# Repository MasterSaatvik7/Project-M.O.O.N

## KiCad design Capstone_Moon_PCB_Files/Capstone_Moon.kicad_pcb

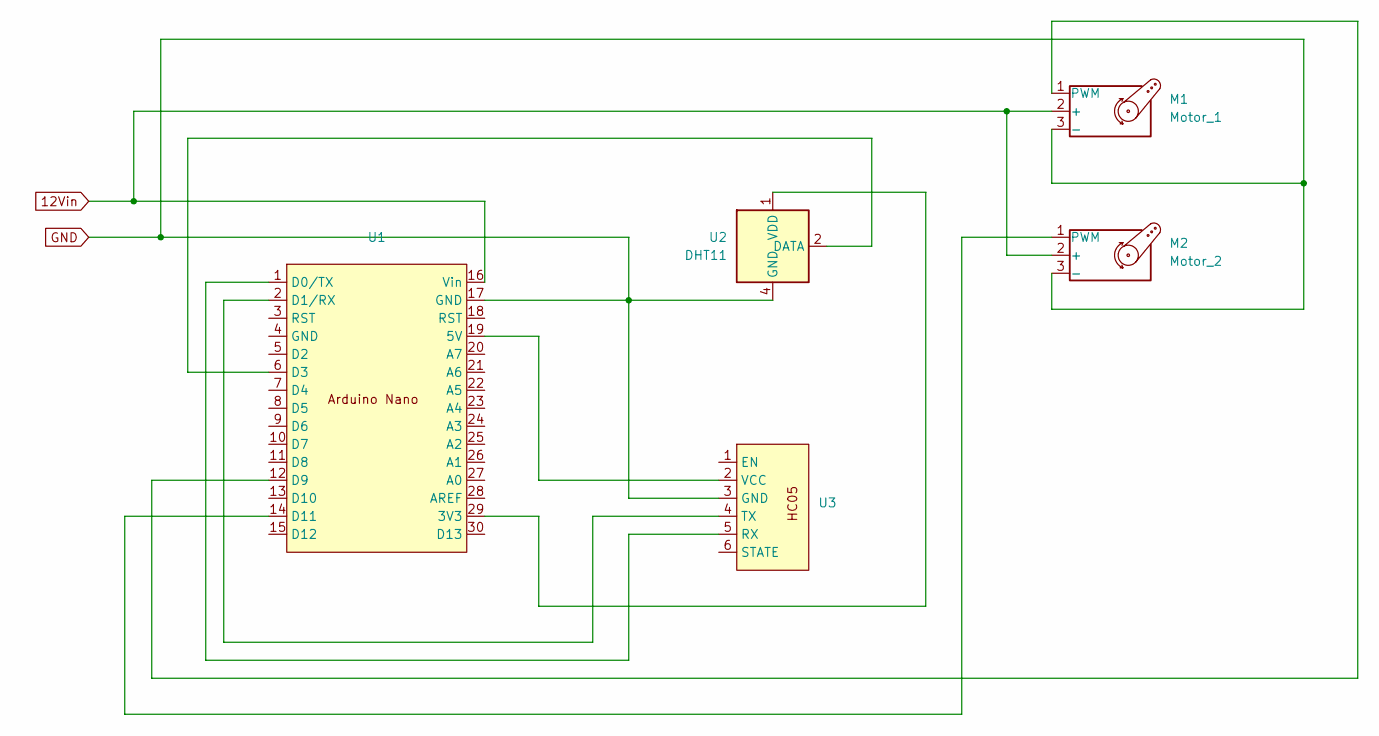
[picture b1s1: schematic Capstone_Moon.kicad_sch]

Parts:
M1: Motor_1; BLDC_temporary_pad
M2: Motor_2; BLDC_temporary_pad
U1: Arduino_Nano
U2: DHT11; Aosong_DHT11_5.5x12.0_P2.54mm
U3: HC05

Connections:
12Vin: M1.2 (+), M2.2 (+), U1.16 (Vin)
GND: M1.3 (-), M2.3 (-), U1.17 (GND), U2.4 (GND), U3.3 (GND)
unnamed: M1.1 (PWM), U1.12 (D9)
unnamed: M2.1 (PWM), U1.14 (D11)
unnamed: U1.29 (3V3), U2.1 (VDD)
unnamed: U1.19 (5V), U3.2 (VCC)
unnamed: U1.1 (D0/TX), U3.5 (RX)
unnamed: U1.2 (D1/RX), U3.4 (TX)
unnamed: U1.6 (D3), U2.2 (DATA)

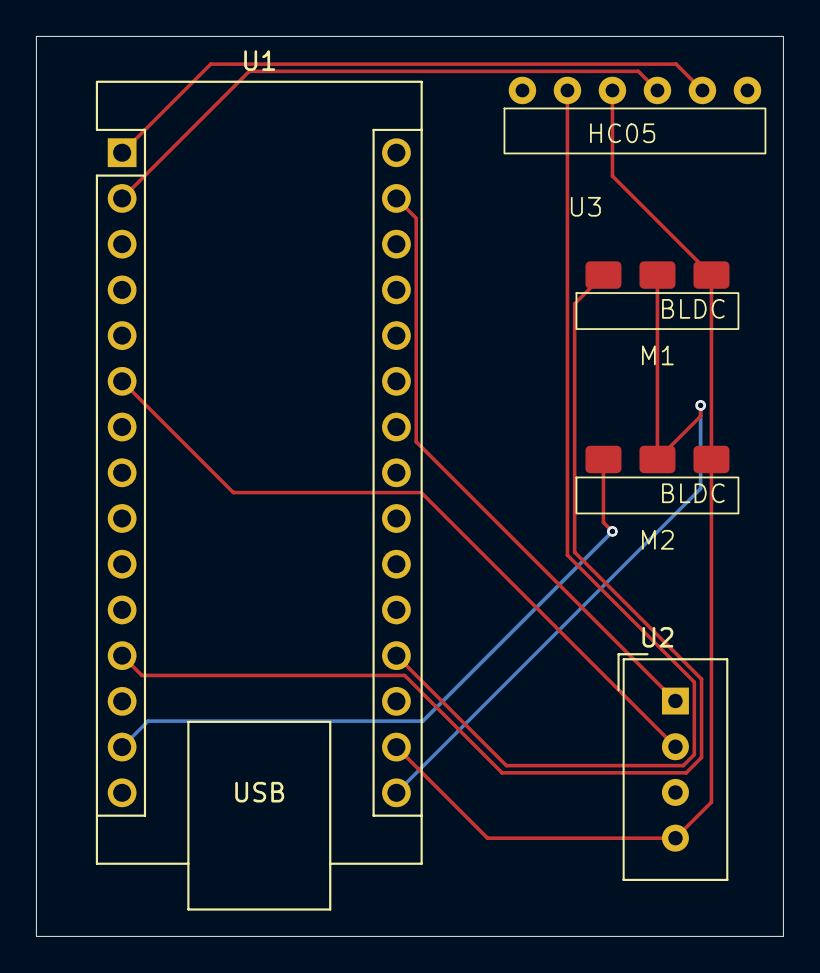
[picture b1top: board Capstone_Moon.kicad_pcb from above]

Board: 2 copper layers, 41.5 x 50.0 mm, 5 parts (0 on the bottom side), 9 nets.

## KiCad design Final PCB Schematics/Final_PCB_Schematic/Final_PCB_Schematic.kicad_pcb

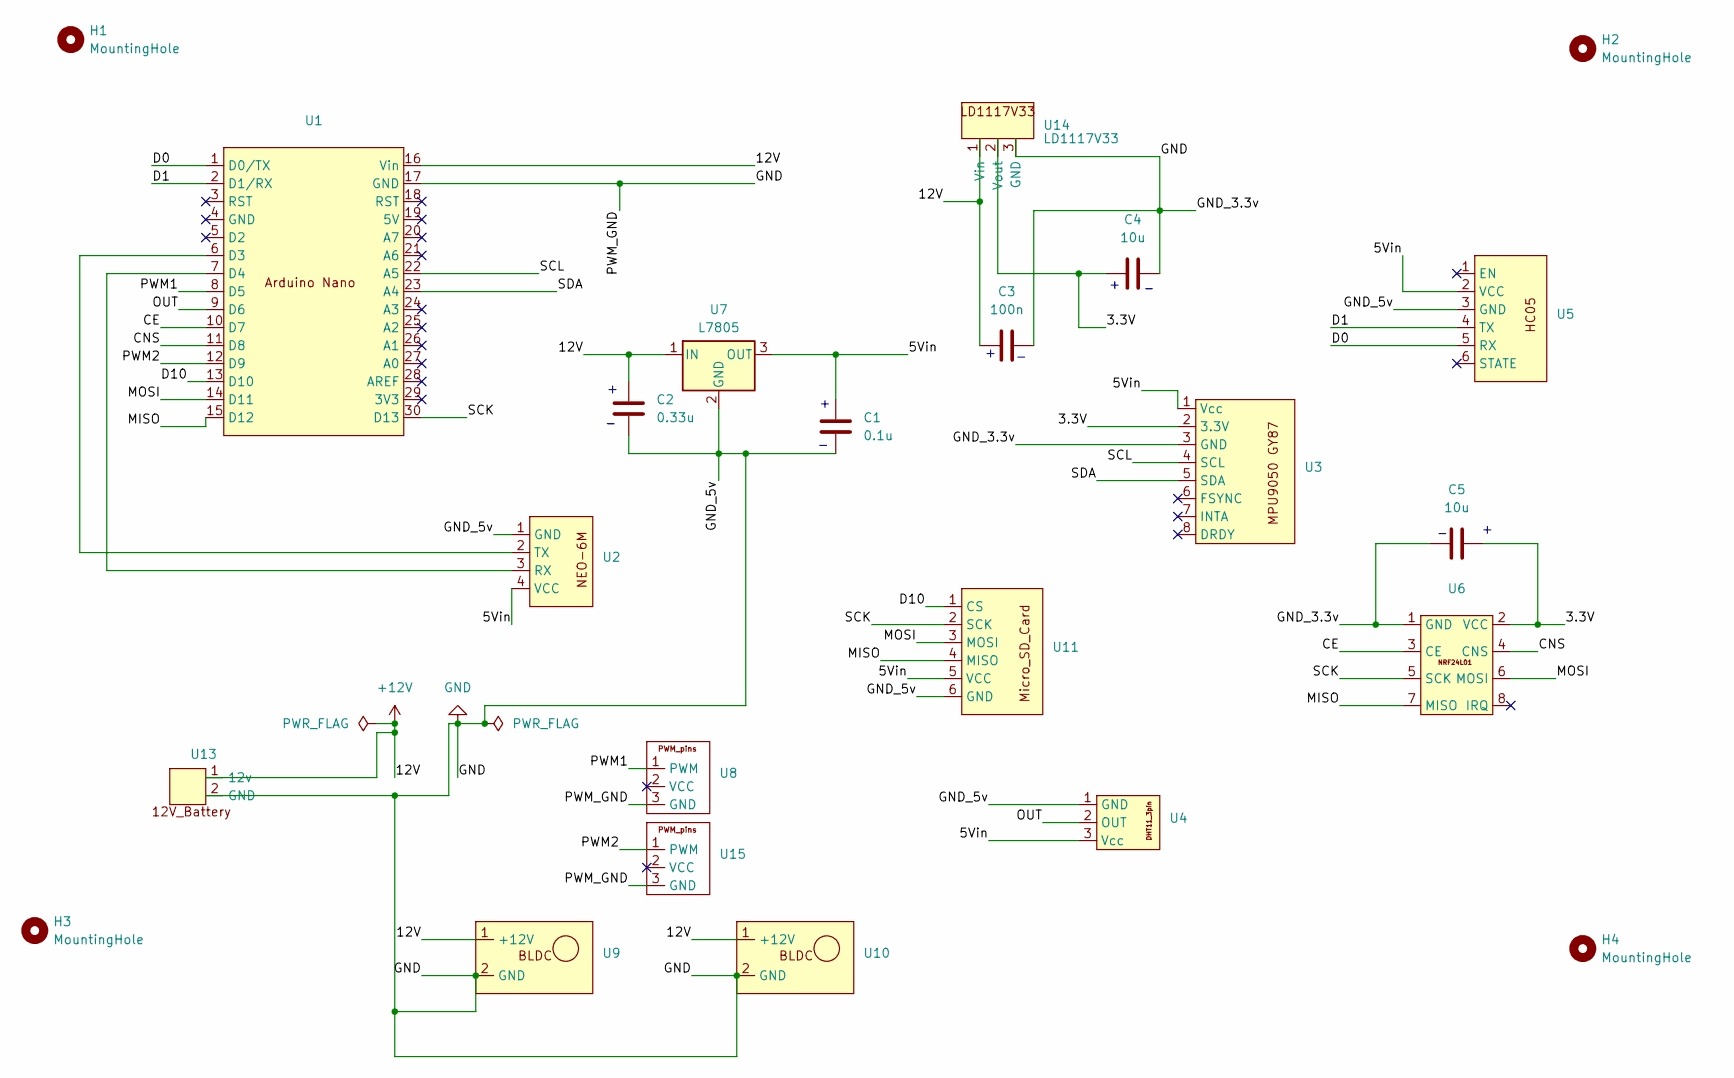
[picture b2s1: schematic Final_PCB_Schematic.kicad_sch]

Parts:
C1: 0.1u; CP_Radial_D5.0mm_P2.50mm
C2: 0.33u; CP_Radial_D5.0mm_P2.50mm
C3: 100n; CP_Radial_D5.0mm_P2.50mm
C4, C5: 10u; CP_Radial_D5.0mm_P2.50mm
H1, H2, H3, H4: MountingHole; MountingHole_3.2mm_M3
U1: capstone_arduino
U2: NEO_6M
U3: MPU9050
U4: DHT11_3pin
U5: HC05
U6: NRF24L01_custom
U7: L7805
U8, U15: PWM_Pins_Through_Hole
U9, U10: BLDC_temporary_pad
U11: Micro_SD_Card_Arduino
U13: 12V_Battery
U14: LD1117V33; LD117V33

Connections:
+12V: C2.1, C3.1, U1.16 (Vin), U7.1 (IN), U9.1 (+12V), U10.1 (+12V), U13.1 (12v), U14.1 (Vin)
/3.3V: C4.1, C5.1, U3.2 (3.3V), U6.2 (VCC), U14.2 (Vout)
/5Vin: C1.1, U2.4 (VCC), U3.1 (Vcc), U4.3 (Vcc), U5.2 (VCC), U7.3 (OUT), U11.5 (VCC)
/CE: U1.10 (D7), U6.3 (CE)
/CNS: U1.11 (D8), U6.4 (CNS)
/D0: U1.1 (D0/TX), U5.5 (RX)
/D1: U1.2 (D1/RX), U5.4 (TX)
/D10: U1.13 (D10), U11.1 (CS)
/MISO: U1.15 (D12), U6.7 (MISO), U11.4 (MISO)
/MOSI: U1.14 (D11), U6.6 (MOSI), U11.3 (MOSI)
/OUT: U1.9 (D6), U4.2 (OUT)
/PWM1: U1.8 (D5), U8.1 (PWM)
/PWM2: U1.12 (D9), U15.1 (PWM)
/SCK: U1.30 (D13), U6.5 (SCK), U11.2 (SCK)
/SCL: U1.22 (A5), U3.4 (SCL)
/SDA: U1.23 (A4), U3.5 (SDA)
GND: C1.2, C2.2, C3.2, C4.2, C5.2, U1.17 (GND), U2.1 (GND), U3.3 (GND), U4.1 (GND), U5.3 (GND), U6.1 (GND), U7.2 (GND), U8.3 (GND), U9.2 (GND), U10.2 (GND), U11.6 (GND), U13.2 (GND), U14.3 (GND), U15.3 (GND)
unnamed: U1.6 (D3), U2.2 (TX)
unnamed: U1.7 (D4), U2.3 (RX)

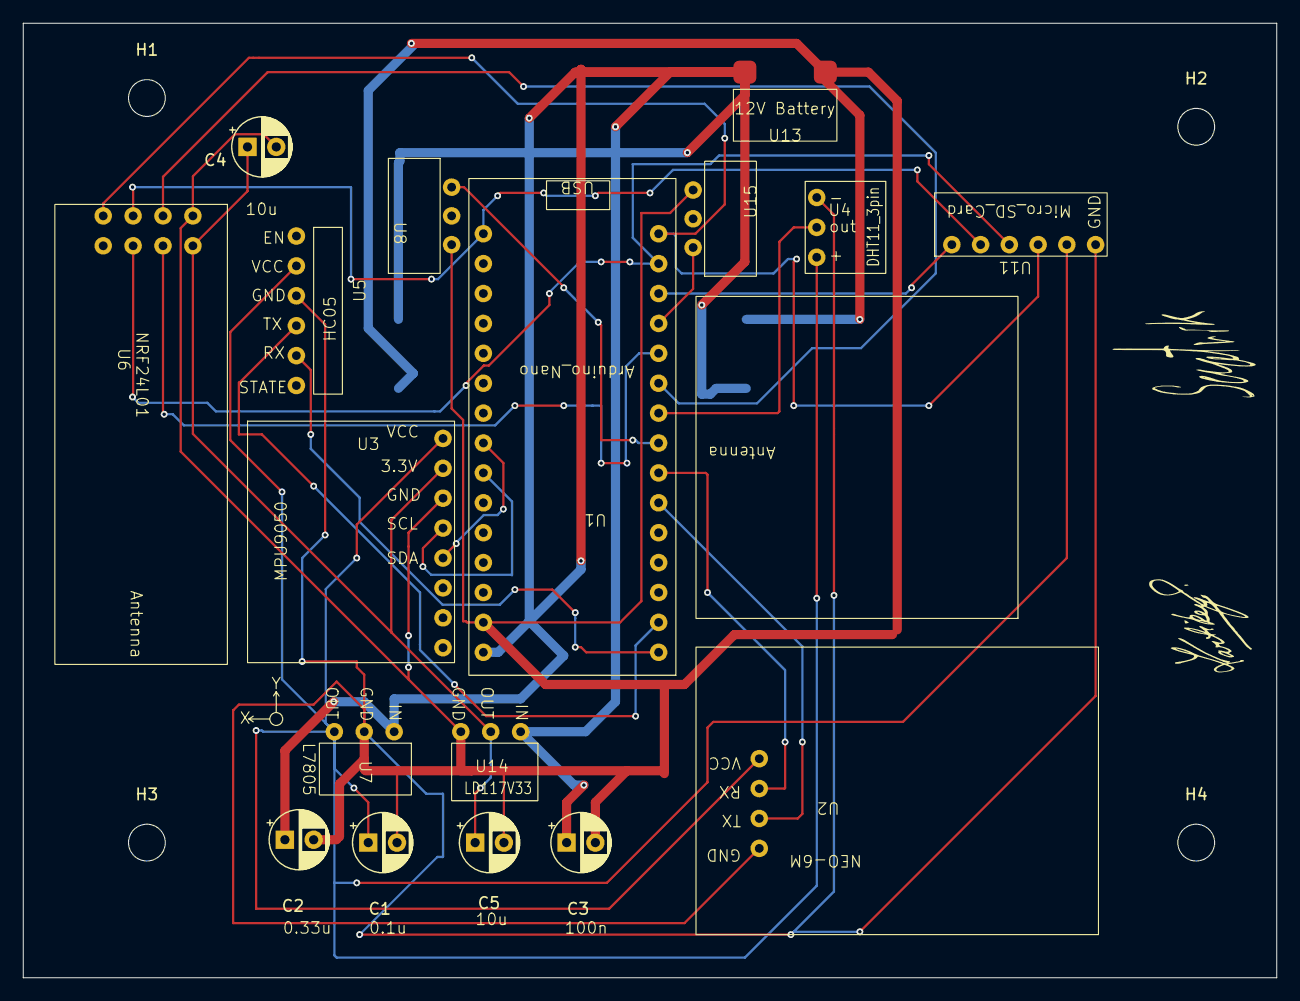
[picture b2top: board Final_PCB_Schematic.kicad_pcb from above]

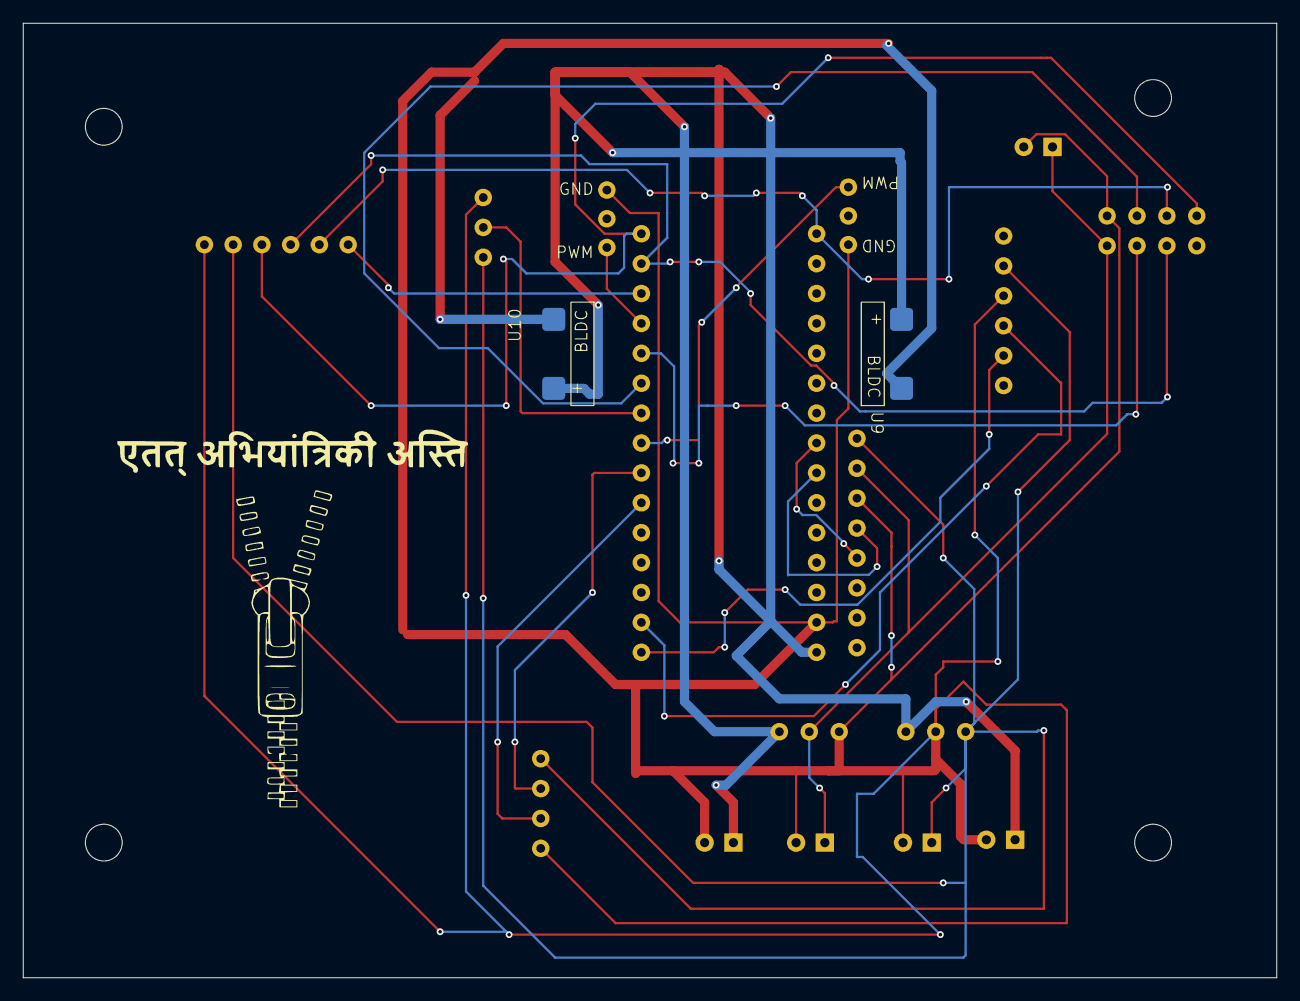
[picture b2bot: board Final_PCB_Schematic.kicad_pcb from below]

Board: 2 copper layers, 109.0 x 83.0 mm, 23 parts (2 on the bottom side), 19 nets.

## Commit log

2025-04-04 Project 1st Upload
2025-04-09 Update: Added new files, removed old files, and modified existing ones
2025-05-15 Updates just before full delete
2025-08-27 3D part file added
